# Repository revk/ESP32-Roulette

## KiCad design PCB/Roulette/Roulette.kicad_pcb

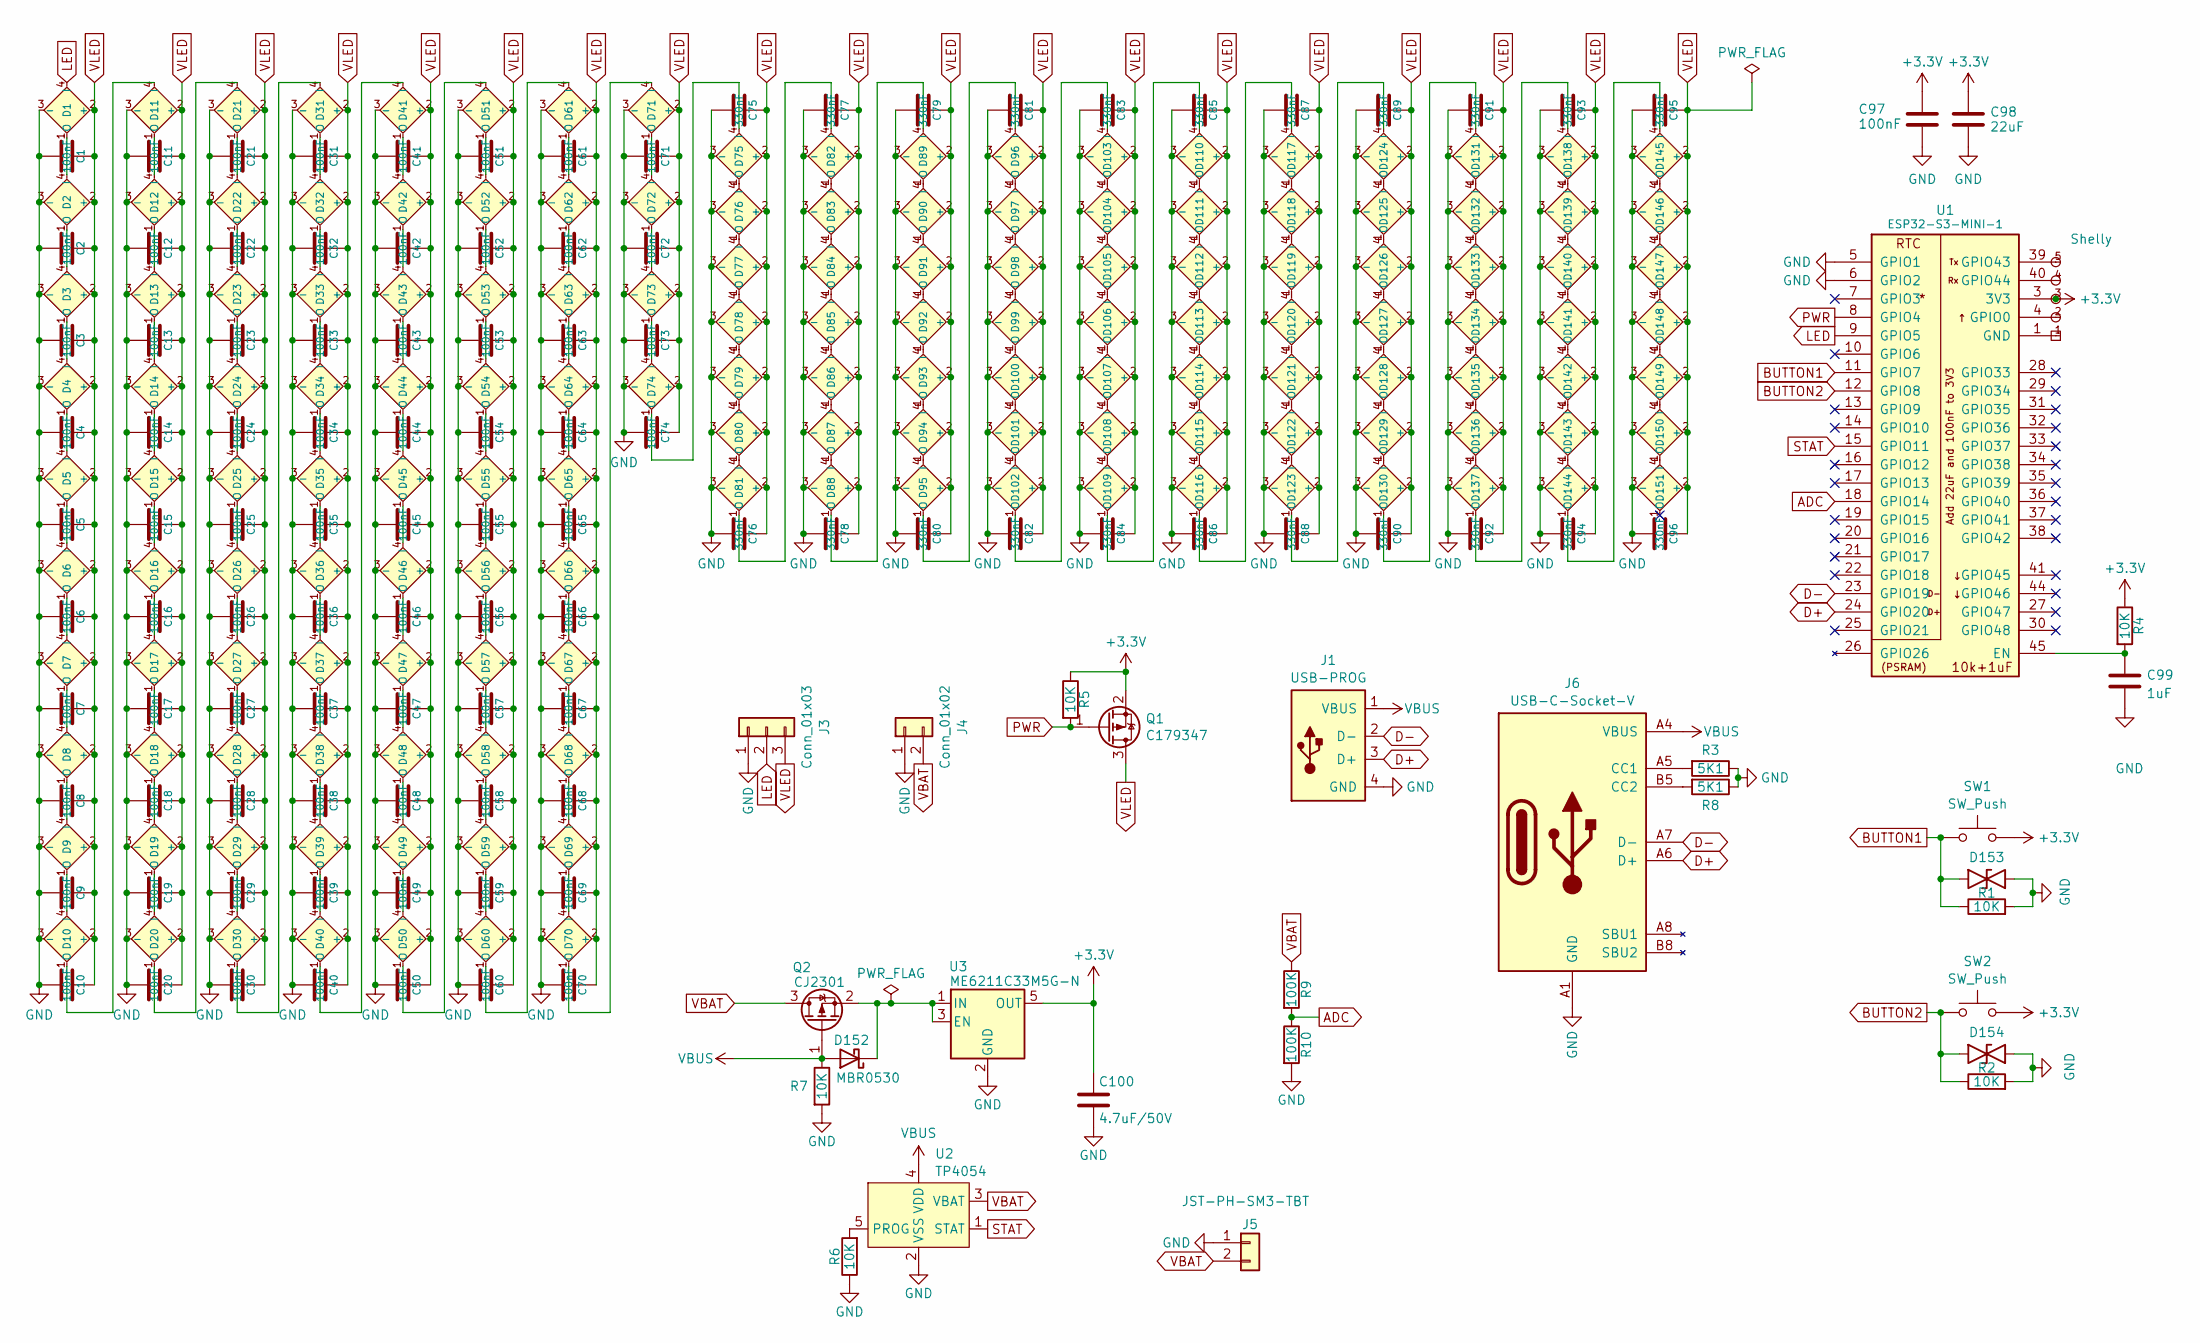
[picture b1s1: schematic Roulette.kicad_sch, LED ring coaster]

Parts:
C1, C2, C3, C4, C5, C6, C7, C8, C9, C10, C11, C12, C13, C14, C15, C16, C17, C18, C19, C20, C21, C22, C23, C24, C25, C26, C27, C28, C29, C30, C31, C32, C33, C34, C35, C36, C37, C38, C39, C40, C41, C42, C43, C44, C45, C46, C47, C48, C49, C50, C51, C52, C53, C54, C55, C56, C57, C58, C59, C60, C61, C62, C63, C64, C65, C66, C67, C68, C69, C70, C71, C72, C73, C74, C97: 100nF
C75, C76, C77, C78, C79, C80, C81, C82, C83, C84, C85, C86, C87, C88, C89, C90, C91, C92, C93, C94, C95, C96: 330nF
C98: 22uF
C99: 1uF
C100: 4.7uF/50V
D1, D2, D3, D4, D5, D6, D7, D8, D9, D10, D11, D12, D13, D14, D15, D16, D17, D18, D19, D20, D21, D22, D23, D24, D25, D26, D27, D28, D29, D30, D31, D32, D33, D34, D35, D36, D37, D38, D39, D40, D41, D42, D43, D44, D45, D46, D47, D48, D49, D50, D51, D52, D53, D54, D55, D56, D57, D58, D59, D60, D61, D62, D63, D64, D65, D66, D67, D68, D69, D70, D71, D72, D73, D74, D75, D76, D77, D78, D79, D80, D81, D82, D83, D84, D85, D86, D87, D88, D89, D90, D91, D92, D93, D94, D95, D96, D97, D98, D99, D100, D101, D102, D103, D104, D105, D106, D107, D108, D109, D110, D111, D112, D113, D114, D115, D116, D117, D118, D119, D120, D121, D122, D123, D124, D125, D126, D127, D128, D129, D130, D131, D132, D133, D134, D135, D136, D137, D138, D139, D140, D141, D142, D143, D144, D145, D146, D147, D148, D149, D150, D151: XL-1010RGBC-WS2812B; MPN C5349953
D152: MBR0530
D153, D154: DFN1006-2L; MPN C5137770
J1: USB-PROG
J2: Shelly
J3: Conn_01x03
J4: Conn_01x02
J5: JST-PH-SM3-TBT
J6: USB-C-Socket-V; MPN C3001289
Q1: C179347
Q2: CJ2301; SOT-23
R1, R2, R4, R5, R6, R7: 10K
R3, R8: 5K1
R9, R10: 100K
SW1, SW2: SW_Push
U1: ESP32-S3-MINI-1; MPN C3013941
U2: TP4054; SOT-23-5; MPN C668215
U3: ME6211C33M5G-N; SOT-23-5

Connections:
+3.3V: C97.1, C98.1, C100.1, J2.3 (3V3), Q1.2 (S), R4.1, R5.1, SW1.2, SW2.2, U1.3 (3V3), U3.5 (OUT)
ADC: R9.2, R10.1, U1.18 (GPIO14)
BUTTON1: D153.2, R1.1, SW1.1, U1.11 (GPIO7)
BUTTON2: D154.2, R2.1, SW2.1, U1.12 (GPIO8)
D+: J1.3 (D+), J6.A6 (D+), J6.B6 (D+), U1.24 (GPIO20)
D-: J1.2 (D-), J6.A7 (D-), J6.B7 (D-), U1.23 (GPIO19)
LED: D1.4 (I), J3.2, U1.9 (GPIO5)
unnamed: D1.1 (O), D2.4 (I)
unnamed: D2.1 (O), D3.4 (I)
unnamed: D3.1 (O), D4.4 (I)
unnamed: D4.1 (O), D5.4 (I)
unnamed: D5.1 (O), D6.4 (I)
unnamed: D6.1 (O), D7.4 (I)
unnamed: D7.1 (O), D8.4 (I)
unnamed: D8.1 (O), D9.4 (I)
unnamed: D9.1 (O), D10.4 (I)
unnamed: D10.1 (O), D11.4 (I)
unnamed: D11.1 (O), D12.4 (I)
unnamed: D12.1 (O), D13.4 (I)
unnamed: D13.1 (O), D14.4 (I)
unnamed: D14.1 (O), D15.4 (I)
unnamed: D15.1 (O), D16.4 (I)
unnamed: D16.1 (O), D17.4 (I)
unnamed: D17.1 (O), D18.4 (I)
unnamed: D18.1 (O), D19.4 (I)
unnamed: D19.1 (O), D20.4 (I)
unnamed: D20.1 (O), D21.4 (I)
unnamed: D21.1 (O), D22.4 (I)
unnamed: D22.1 (O), D23.4 (I)
unnamed: D23.1 (O), D24.4 (I)
unnamed: D24.1 (O), D25.4 (I)
unnamed: D25.1 (O), D26.4 (I)
unnamed: D26.1 (O), D27.4 (I)
unnamed: D27.1 (O), D28.4 (I)
unnamed: D28.1 (O), D29.4 (I)
unnamed: D29.1 (O), D30.4 (I)
unnamed: D30.1 (O), D31.4 (I)
unnamed: D31.1 (O), D32.4 (I)
unnamed: D32.1 (O), D33.4 (I)
unnamed: D33.1 (O), D34.4 (I)
unnamed: D34.1 (O), D35.4 (I)
unnamed: D35.1 (O), D36.4 (I)
unnamed: D36.1 (O), D37.4 (I)
unnamed: D37.1 (O), D38.4 (I)
unnamed: D38.1 (O), D39.4 (I)
unnamed: D39.1 (O), D40.4 (I)
unnamed: D40.1 (O), D41.4 (I)
unnamed: D41.1 (O), D42.4 (I)
unnamed: D42.1 (O), D43.4 (I)
unnamed: D43.1 (O), D44.4 (I)
unnamed: D44.1 (O), D45.4 (I)
unnamed: D45.1 (O), D46.4 (I)
unnamed: D46.1 (O), D47.4 (I)
unnamed: D47.1 (O), D48.4 (I)
unnamed: D48.1 (O), D49.4 (I)
unnamed: D49.1 (O), D50.4 (I)
unnamed: D50.1 (O), D51.4 (I)
unnamed: D51.1 (O), D52.4 (I)
unnamed: D52.1 (O), D53.4 (I)
unnamed: D53.1 (O), D54.4 (I)
unnamed: D54.1 (O), D55.4 (I)
unnamed: D55.1 (O), D56.4 (I)
unnamed: D56.1 (O), D57.4 (I)
unnamed: D57.1 (O), D58.4 (I)
unnamed: D58.1 (O), D59.4 (I)
unnamed: D59.1 (O), D60.4 (I)
unnamed: D60.1 (O), D61.4 (I)
unnamed: D61.1 (O), D62.4 (I)
unnamed: D62.1 (O), D63.4 (I)
unnamed: D63.1 (O), D64.4 (I)
unnamed: D64.1 (O), D65.4 (I)
unnamed: D65.1 (O), D66.4 (I)
unnamed: D66.1 (O), D67.4 (I)
unnamed: D67.1 (O), D68.4 (I)
unnamed: D68.1 (O), D69.4 (I)
unnamed: D69.1 (O), D70.4 (I)
unnamed: D70.1 (O), D71.4 (I)
unnamed: D71.1 (O), D72.4 (I)
unnamed: D72.1 (O), D73.4 (I)
unnamed: D73.1 (O), D74.4 (I)
unnamed: D74.1 (O), D75.4 (I)
unnamed: D75.1 (O), D76.4 (I)
unnamed: D76.1 (O), D77.4 (I)
unnamed: D77.1 (O), D78.4 (I)
unnamed: D78.1 (O), D79.4 (I)
unnamed: D79.1 (O), D80.4 (I)
unnamed: D80.1 (O), D81.4 (I)
unnamed: D81.1 (O), D82.4 (I)
unnamed: D82.1 (O), D83.4 (I)
unnamed: D83.1 (O), D84.4 (I)
unnamed: D84.1 (O), D85.4 (I)
unnamed: D85.1 (O), D86.4 (I)
unnamed: D86.1 (O), D87.4 (I)
unnamed: D87.1 (O), D88.4 (I)
unnamed: D88.1 (O), D89.4 (I)
unnamed: D89.1 (O), D90.4 (I)
unnamed: D90.1 (O), D91.4 (I)
unnamed: D91.1 (O), D92.4 (I)
unnamed: D92.1 (O), D93.4 (I)
unnamed: D93.1 (O), D94.4 (I)
unnamed: D94.1 (O), D95.4 (I)
unnamed: D95.1 (O), D96.4 (I)
unnamed: D96.1 (O), D97.4 (I)
unnamed: D97.1 (O), D98.4 (I)
unnamed: D98.1 (O), D99.4 (I)
unnamed: D99.1 (O), D100.4 (I)
unnamed: D100.1 (O), D101.4 (I)
unnamed: D101.1 (O), D102.4 (I)
unnamed: D102.1 (O), D103.4 (I)
unnamed: D103.1 (O), D104.4 (I)
unnamed: D104.1 (O), D105.4 (I)
unnamed: D105.1 (O), D106.4 (I)
unnamed: D106.1 (O), D107.4 (I)
unnamed: D107.1 (O), D108.4 (I)
unnamed: D108.1 (O), D109.4 (I)
unnamed: D109.1 (O), D110.4 (I)
unnamed: D110.1 (O), D111.4 (I)
unnamed: D111.1 (O), D112.4 (I)
unnamed: D112.1 (O), D113.4 (I)
unnamed: D113.1 (O), D114.4 (I)
unnamed: D114.1 (O), D115.4 (I)
unnamed: D115.1 (O), D116.4 (I)
unnamed: D116.1 (O), D117.4 (I)
unnamed: D117.1 (O), D118.4 (I)
unnamed: D118.1 (O), D119.4 (I)
unnamed: D119.1 (O), D120.4 (I)
unnamed: D120.1 (O), D121.4 (I)
unnamed: D121.1 (O), D122.4 (I)
unnamed: D122.1 (O), D123.4 (I)
unnamed: D123.1 (O), D124.4 (I)
unnamed: D124.1 (O), D125.4 (I)
unnamed: D125.1 (O), D126.4 (I)
unnamed: D126.1 (O), D127.4 (I)
unnamed: D127.1 (O), D128.4 (I)
unnamed: D128.1 (O), D129.4 (I)
unnamed: D129.1 (O), D130.4 (I)
unnamed: D130.1 (O), D131.4 (I)
unnamed: D131.1 (O), D132.4 (I)
unnamed: D132.1 (O), D133.4 (I)
unnamed: D133.1 (O), D134.4 (I)
unnamed: D134.1 (O), D135.4 (I)
unnamed: D135.1 (O), D136.4 (I)
unnamed: D136.1 (O), D137.4 (I)
unnamed: D137.1 (O), D138.4 (I)
unnamed: D138.1 (O), D139.4 (I)
unnamed: D139.1 (O), D140.4 (I)
unnamed: D140.1 (O), D141.4 (I)
unnamed: D141.1 (O), D142.4 (I)
unnamed: D142.1 (O), D143.4 (I)
unnamed: D143.1 (O), D144.4 (I)
unnamed: D144.1 (O), D145.4 (I)
unnamed: D145.1 (O), D146.4 (I)
unnamed: D146.1 (O), D147.4 (I)
unnamed: D147.1 (O), D148.4 (I)
unnamed: D148.1 (O), D149.4 (I)
unnamed: D149.1 (O), D150.4 (I)
unnamed: D150.1 (O), D151.4 (I)
unnamed: D152.1 (K), Q2.2 (S), U3.1 (IN), U3.3 (EN)
unnamed: J2.2 (0), U1.4 (GPIO0)
unnamed: J2.4 (Rx), U1.40 (GPIO44)
unnamed: J2.5 (Tx), U1.39 (GPIO43)
unnamed: J6.A5 (CC1), R3.2
unnamed: J6.B5 (CC2), R8.2
unnamed: C99.1, R4.2, U1.45 (EN)
unnamed: R6.2, U2.5 (PROG)
PWR: Q1.1 (G), R5.2, U1.8 (GPIO4)
STAT: U1.15 (GPIO11), U2.1 (STAT)
VBAT: J4.2, J5.2, Q2.3 (D), R9.1, U2.3 (VBAT)
VBUS: D152.2 (A), J1.1 (VBUS), J6.A4 (VBUS), J6.A9 (VBUS), J6.B4 (VBUS), J6.B9 (VBUS), Q2.1 (G), R7.1, U2.4 (VDD)
VLED: C1.1, C2.1, C3.1, C4.1, C5.1, C6.1, C7.1, C8.1, C9.1, C10.1, C11.1, C12.1, C13.1, C14.1, C15.1, C16.1, C17.1, C18.1, C19.1, C20.1, C21.1, C22.1, C23.1, C24.1, C25.1, C26.1, C27.1, C28.1, C29.1, C30.1, C31.1, C32.1, C33.1, C34.1, C35.1, C36.1, C37.1, C38.1, C39.1, C40.1, C41.1, C42.1, C43.1, C44.1, C45.1, C46.1, C47.1, C48.1, C49.1, C50.1, C51.1, C52.1, C53.1, C54.1, C55.1, C56.1, C57.1, C58.1, C59.1, C60.1, C61.1, C62.1, C63.1, C64.1, C65.1, C66.1, C67.1, C68.1, C69.1, C70.1, C71.1, C72.1, C73.1, C74.1, C75.1, C76.1, C77.1, C78.1, C79.1, C80.1, C81.1, C82.1, C83.1, C84.1, C85.1, C86.1, C87.1, C88.1, C89.1, C90.1, C91.1, C92.1, C93.1, C94.1, C95.1, C96.1, D1.2 (+), D2.2 (+), D3.2 (+), D4.2 (+), D5.2 (+), D6.2 (+), D7.2 (+), D8.2 (+), D9.2 (+), D10.2 (+), D11.2 (+), D12.2 (+), D13.2 (+), D14.2 (+), D15.2 (+), D16.2 (+), D17.2 (+), D18.2 (+), D19.2 (+), D20.2 (+), D21.2 (+), D22.2 (+), D23.2 (+), D24.2 (+), D25.2 (+), D26.2 (+), D27.2 (+), D28.2 (+), D29.2 (+), D30.2 (+), D31.2 (+), D32.2 (+), D33.2 (+), D34.2 (+), D35.2 (+), D36.2 (+), D37.2 (+), D38.2 (+), D39.2 (+), D40.2 (+), D41.2 (+), D42.2 (+), D43.2 (+), D44.2 (+), D45.2 (+), D46.2 (+), D47.2 (+), D48.2 (+), D49.2 (+), D50.2 (+), D51.2 (+), D52.2 (+), D53.2 (+), D54.2 (+), D55.2 (+), D56.2 (+), D57.2 (+), D58.2 (+), D59.2 (+), D60.2 (+), D61.2 (+), D62.2 (+), D63.2 (+), D64.2 (+), D65.2 (+), D66.2 (+), D67.2 (+), D68.2 (+), D69.2 (+), D70.2 (+), D71.2 (+), D72.2 (+), D73.2 (+), D74.2 (+), D75.2 (+), D76.2 (+), D77.2 (+), D78.2 (+), D79.2 (+), D80.2 (+), D81.2 (+), D82.2 (+), D83.2 (+), D84.2 (+), D85.2 (+), D86.2 (+), D87.2 (+), D88.2 (+), D89.2 (+), D90.2 (+), D91.2 (+), D92.2 (+), D93.2 (+), D94.2 (+), D95.2 (+), D96.2 (+), D97.2 (+), D98.2 (+), D99.2 (+), D100.2 (+), D101.2 (+), D102.2 (+), D103.2 (+), D104.2 (+), D105.2 (+), D106.2 (+), D107.2 (+), D108.2 (+), D109.2 (+), D110.2 (+), D111.2 (+), D112.2 (+), D113.2 (+), D114.2 (+), D115.2 (+), D116.2 (+), D117.2 (+), D118.2 (+), D119.2 (+), D120.2 (+), D121.2 (+), D122.2 (+), D123.2 (+), D124.2 (+), D125.2 (+), D126.2 (+), D127.2 (+), D128.2 (+), D129.2 (+), D130.2 (+), D131.2 (+), D132.2 (+), D133.2 (+), D134.2 (+), D135.2 (+), D136.2 (+), D137.2 (+), D138.2 (+), D139.2 (+), D140.2 (+), D141.2 (+), D142.2 (+), D143.2 (+), D144.2 (+), D145.2 (+), D146.2 (+), D147.2 (+), D148.2 (+), D149.2 (+), D150.2 (+), D151.2 (+), J3.3, Q1.3 (D)

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
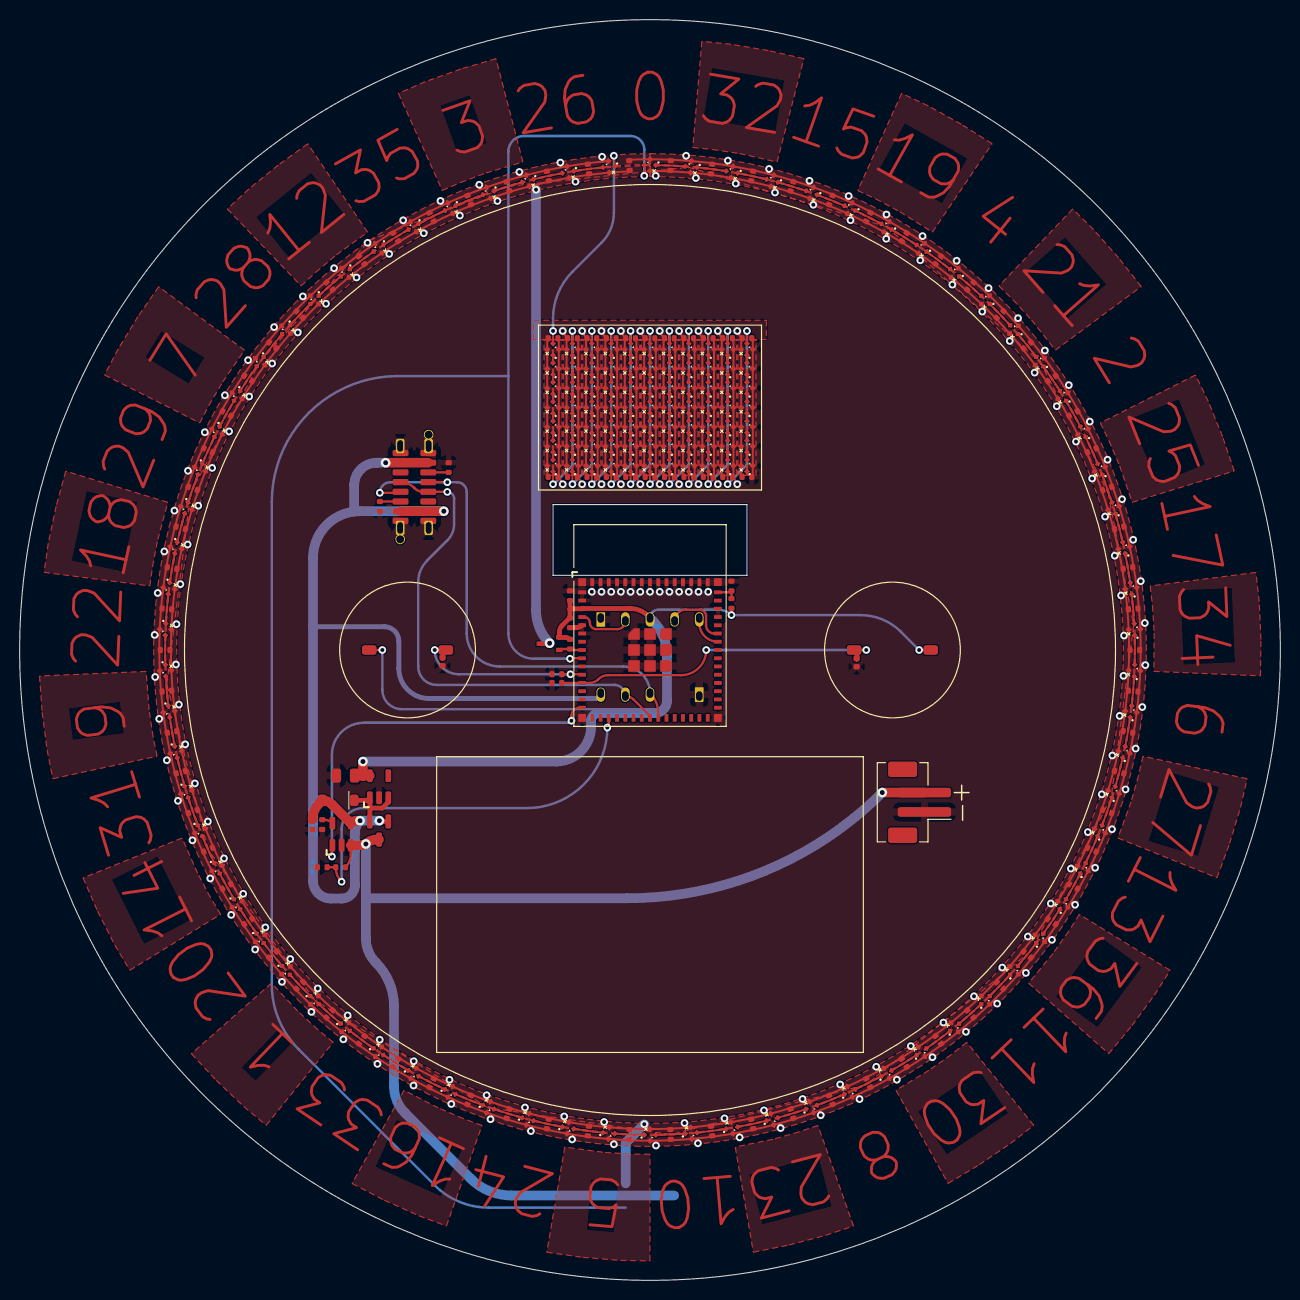
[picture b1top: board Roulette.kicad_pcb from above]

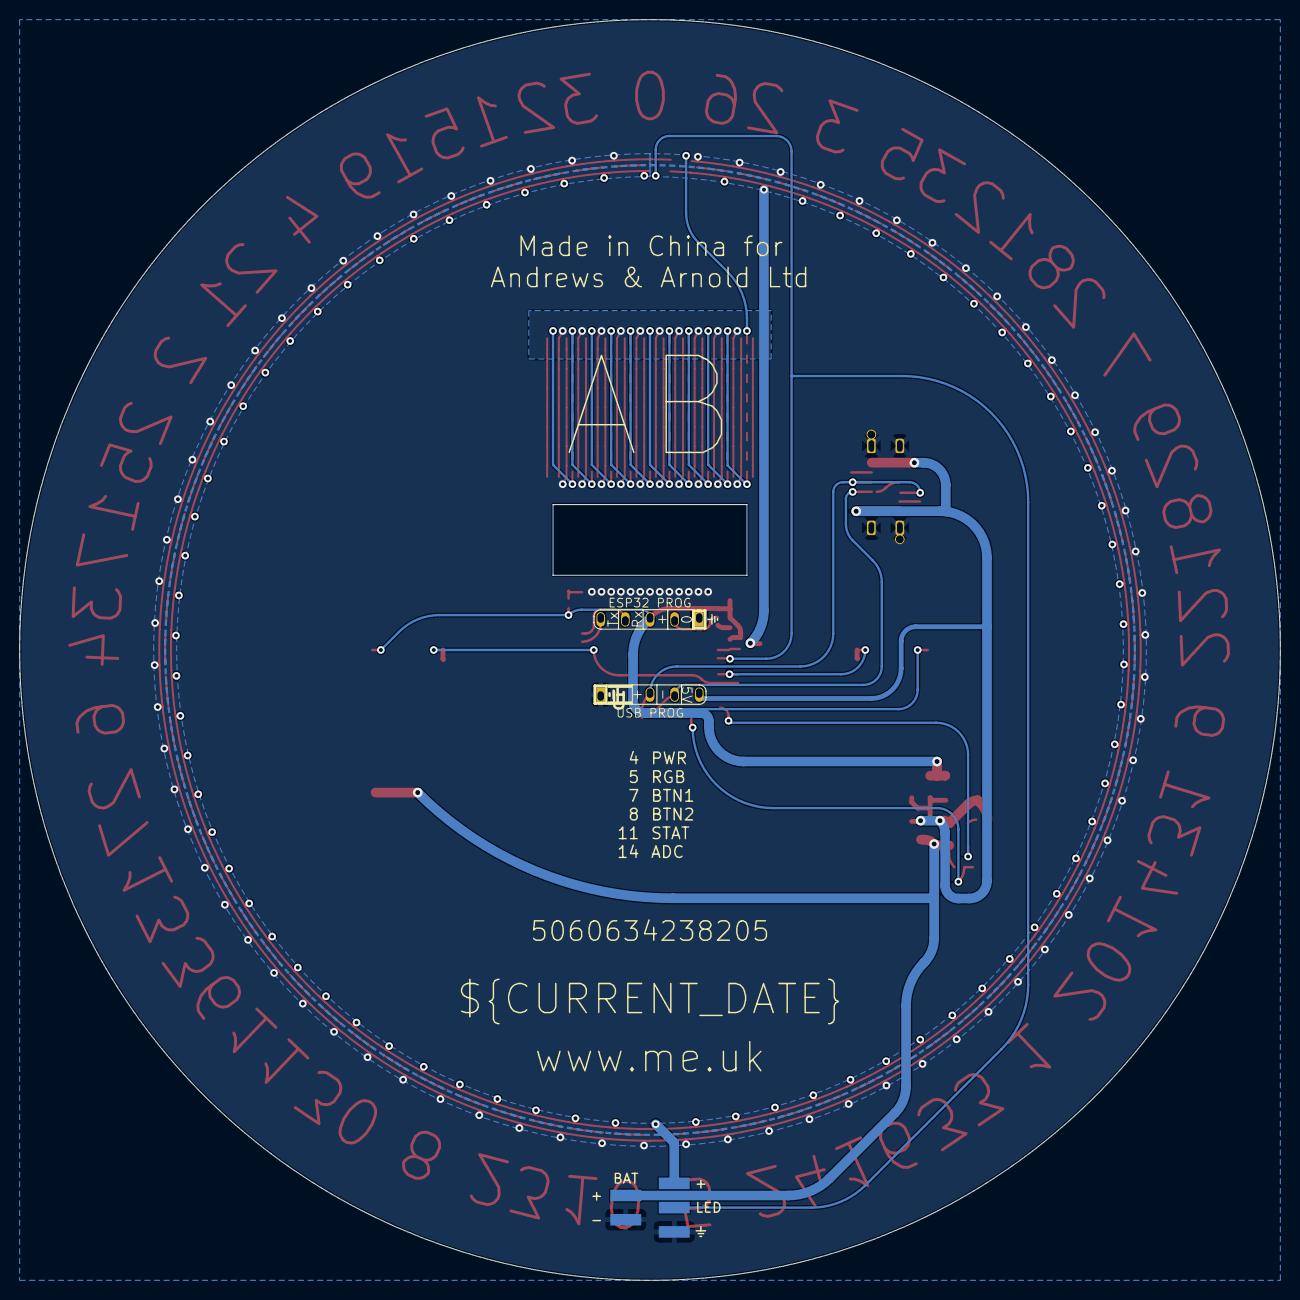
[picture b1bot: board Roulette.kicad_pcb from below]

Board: 2 copper layers, 130.0 x 130.0 mm, 277 parts (4 on the bottom side), 171 nets.

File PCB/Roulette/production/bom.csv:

Designator,Footprint,Quantity,Value,LCSC Part #
"C1, C10, C11, C12, C13, C14, C15, C16, C17, C18, C19, C2, C20, C21, C22, C23, C24, C25, C26, C27, C28, C29, C3, C30, C31, C32, C33, C34, C35, C36, C37, C38, C39, C4, C40, C41, C42, C43, C44, C45, C46, C47, C48, C49, C5, C50, C51, C52, C53, C54, C55, C56, C57, C58, C59, C6, C60, C61, C62, C63, C64, C65, C66, C67, C68, C69, C7, C70, C71, C72, C73, C74, C8, C9, C97",C_0402,75,100nF,
C100,C_0805,1,4.7uF/50V,
"C75, C76, C77, C78, C79, C80, C81, C82, C83, C84, C85, C86, C87, C88, C89, C90, C91, C92, C93, C94, C95, C96",C_0402,22,330nF,
C98,C_0402,1,22uF,
C99,C_0402,1,1uF,
"D1, D10, D100, D101, D102, D103, D104, D105, D106, D107, D108, D109, D11, D110, D111, D112, D113, D114, D115, D116, D117, D118, D119, D12, D120, D121, D122, D123, D124, D125, D126, D127, D128, D129, D13, D130, D131, D132, D133, D134, D135, D136, D137, D138, D139, D14, D140, D141, D142, D143, D144, D145, D146, D147, D148, D149, D15, D150, D151, D16, D17, D18, D19, D2, D20, D21, D22, D23, D24, D25, D26, D27, D28, D29, D3, D30, D31, D32, D33, D34, D35, D36, D37, D38, D39, D4, D40, D41, D42, D43, D44, D45, D46, D47, D48, D49, D5, D50, D51, D52, D53, D54, D55, D56, D57, D58, D59, D6, D60, D61, D62, D63, D64, D65, D66, D67, D68, D69, D7, D70, D71, D72, D73, D74, D75, D76, D77, D78, D79, D8, D80, D81, D82, D83, D84, D85, D86, D87, D88, D89, D9, D90, D91, D92, D93, D94, D95, D96, D97, D98, D99",SMD1010,151,XL-1010RGBC-WS2812B,C5349953
D152,D_SOD-123,1,MBR0530,
"D153, D154",DFN1006-2L,2,~,C5137770
J1,USB-PROG,1,USB-PROG,
J3,3-PADS,1,Conn_01x03,
J4,2-PADS,1,Conn_01x02,
J5,JST_PH_B2B-PH-SM4-TB_1x02-1MP_P2.00mm_Vertical,1,JST-PH-SM3-TBT,C265003
J6,USB-C-Socket-V,1,USB-C-Socket-V,C3001289
Q1,SOT-323_SC-70,1,C179347,C179347
Q2,SOT-23,1,CJ2301,
"R1, R2, R4, R5, R6, R7",R_0402,6,10K,
"R10, R9",R_0402,2,100K,
"R3, R8",R_0402,2,5K1,
"SW1, SW2",TS-1092S-B3D2-G,2,SW_Push,C520860
U1,ESP32-S3-MINI-1,1,ESP32-S3-MINI-1,C3013941
U2,SOT-23-5,1,TP4054,C668215
U3,SOT-23-5,1,ME6211C33M5G-N,

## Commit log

2023-10-22 Started
2023-10-22 Tidy
2023-10-22 led_strip
2023-10-22 D'Oh
2023-10-22 Empty code
2023-10-22 Mask removed
2023-10-22 Tidy graphics
2023-10-22 Image
2023-10-26 Library update
2023-10-26 Started, with test pattern
2023-10-26 Place
2023-10-26 Started new h/w - needs parts and tracking
2023-10-26 Fix parts
2023-10-26 Rechargable board
2023-10-26 Part
2023-10-26 Ordered
2023-10-26 Pad fix
2023-10-26 Basic working, not battery based yet
2023-10-27 Some progress
2023-10-27 Debug
2023-10-27 Start quicker
2023-10-27 Tidy flash
2023-10-27 Buttons active high for ext1 login in ESP
2023-10-27 delay
2023-10-27 Fix 26 colour
2023-10-27 Tidy layout
2023-11-01 New boards
2023-11-01 Correct btn2
2023-11-01 Start on new board logic
2023-11-01 New GPIO
2023-11-01 checkpoint
2023-11-01 Release
2023-11-03 FFS 37?
2023-11-04 Part IDs
2024-02-13 Beta
2025-01-19 Broken
2025-01-23 PCB Update
2026-02-13 submodule
